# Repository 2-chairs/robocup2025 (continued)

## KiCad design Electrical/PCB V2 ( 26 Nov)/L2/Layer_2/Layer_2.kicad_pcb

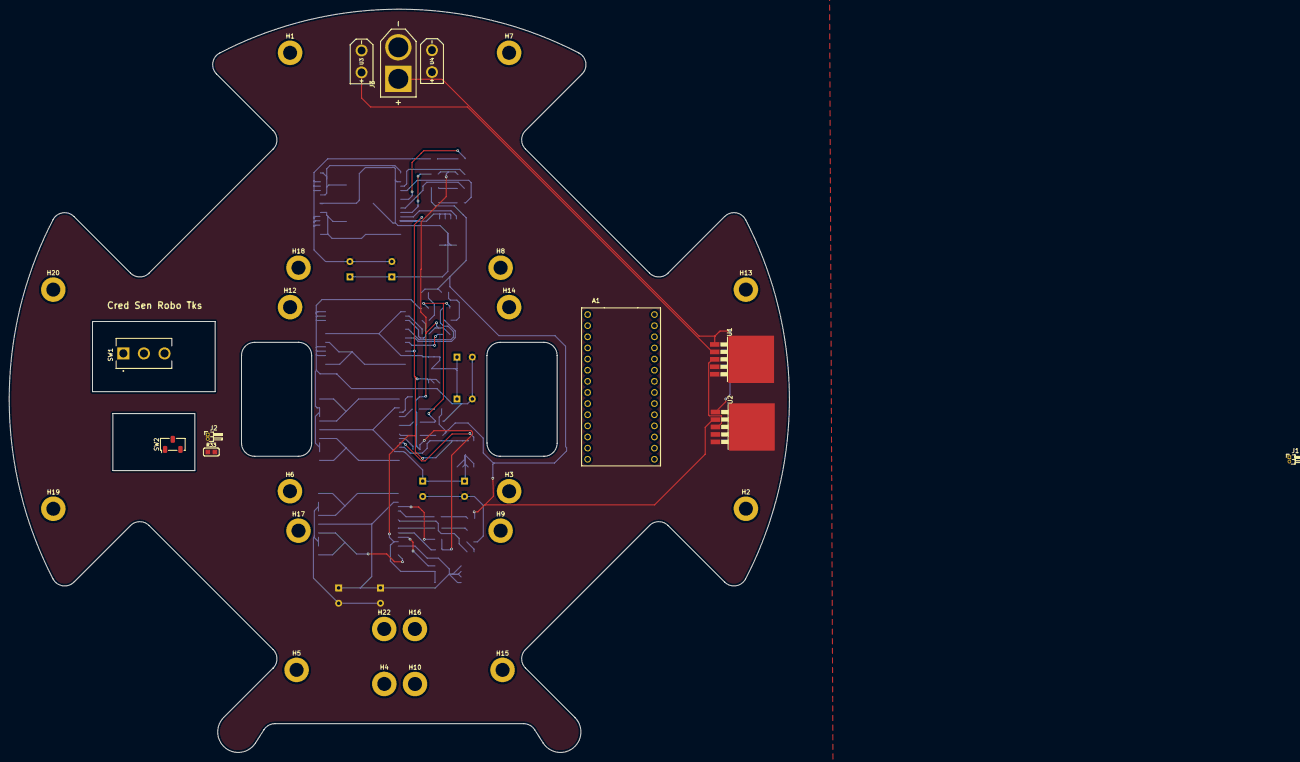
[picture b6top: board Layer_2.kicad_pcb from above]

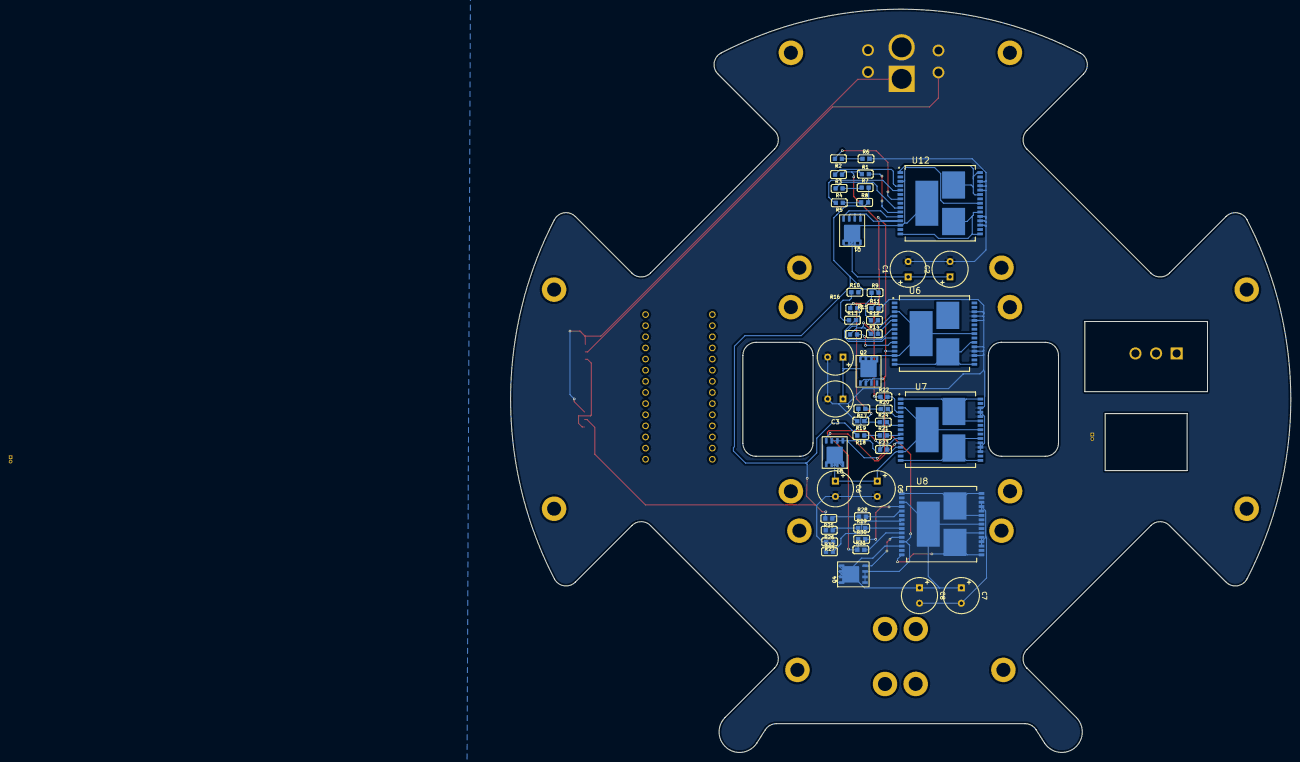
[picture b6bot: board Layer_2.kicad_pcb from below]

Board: 2 copper layers, 178.0 x 169.6 mm, 79 parts (48 on the bottom side), 55 nets.

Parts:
A1: TEENSY_4.0; Teensy 4.0
C1, C2, C3, C4, C5, C6, C7, C8: 470u; CP_Radial_D8.0mm_P3.50mm
H1, H2, H3, H4, H5, H6, H7, H8, H9, H10, H12, H13, H14, H15, H16, H17, H18, H19, H20, H22: MountingHole; MountingHole_3.2mm_M3_DIN965_Pad
J1, J2: Conn_01x02; PinHeader_1x02_P1.00mm_Horizontal
J3: XT60-M; AMASS_XT60-M
Q1, Q2, Q3, Q4: AON6354; 8-DFN (5x6)
R1, R2, R3, R4, R5, R12, R13, R14, R15, R16, R20, R21, R22, R23, R24, R28, R29, R30, R31, R32, R33: 1K; res0603
R6, R11, R19, R27: 10K; res0603
R7, R8, R9, R10, R17, R18, R25, R26: 3K3; res0603
SW1: SW_Push; SW_100SP1T1B4M2QE
SW2: SW_Nidec_CAS-120A1; Nidec_Copal_CAS-120A
U1, U2: LM2596ADJ
U3, U4: XT30UPB-M
U6, U7, U8, U12: VNH5019ATR-E; IC_VNH5019ATR-E

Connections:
+3V3: R7.2, R8.2, R9.2, R10.2, R17.2, R18.2, R25.2, R26.2, U2.2 (OUT), U4.P$1 (+)
+12V: Q1.1 (S), Q1.2 (S), Q1.3 (S), Q2.1 (S), Q2.2 (S), Q2.3 (S), Q3.1 (S), Q3.2 (S), Q3.3 (S), Q4.1 (S), Q4.2 (S), Q4.3 (S), R33.2, U6.12 (VBAT), U7.12 (VBAT), U8.12 (VBAT), U12.12 (VBAT)
/5v: U1.2 (OUT), U3.P$1 (+)
/12v: J3.P (POS), SW1.2, U1.1 (VIN), U2.1 (VIN)
/Motor 1 ENA: R5.1, R8.1
/Motor 1 ENB: R4.1, R7.1
/Motor 1 Out A: U12.1 (OUTA), U12.25 (OUTA), U12.30 (OUTA), U12.HS2 (OUTA)
/Motor 1 Out B: U12.15 (OUTB), U12.16 (OUTB), U12.21 (OUTB), U12.HS3 (OUTB)
/Motor 2 ENA: R9.1, R12.1
/Motor 2 ENB: R10.1, R13.1
/Motor 2 Out A: U6.1 (OUTA), U6.25 (OUTA), U6.30 (OUTA), U6.HS2 (OUTA)
/Motor 2 Out B: U6.15 (OUTB), U6.16 (OUTB), U6.21 (OUTB), U6.HS3 (OUTB)
/Motor 3 ENA: R17.1, R20.1
/Motor 3 ENB: R18.1, R21.1
/Motor 3 Out A: U7.1 (OUTA), U7.25 (OUTA), U7.30 (OUTA), U7.HS2 (OUTA)
/Motor 3 Out B: U7.15 (OUTB), U7.16 (OUTB), U7.21 (OUTB), U7.HS3 (OUTB)
/Motor 4 ENA: R25.1, R28.1
/Motor 4 ENB: R26.1, R29.1
/Motor 4 Out A: U8.1 (OUTA), U8.25 (OUTA), U8.30 (OUTA), U8.HS2 (OUTA)
/Motor 4 Out B: U8.15 (OUTB), U8.16 (OUTB), U8.21 (OUTB), U8.HS3 (OUTB)
/Motor Driver: J2.1, R1.1, R3.1, R14.1, R15.1, R22.1, R23.1, R30.1, R31.1
/PWM Motor 1: R2.1, R6.1
/PWM Motor 2: R11.1, R16.1, R19.1, R24.1
/PWM Motor 4: R27.1, R32.1
GND: C1.2, C2.2, C3.2, C4.2, C5.2, C6.2, C7.2, C8.2, J3.N (NEG), R6.2, R11.2, R19.2, R27.2, U1.3 (GND), U1.6 (GND), U2.3 (GND), U2.6 (GND), U3.P$2 (-), U4.P$2 (-), U6.18 (GNDB), U6.19 (GNDB), U6.20 (GNDB), U6.26 (GNDA), U6.27 (GNDA), U6.28 (GNDA), U7.18 (GNDB), U7.19 (GNDB), U7.20 (GNDB), U7.26 (GNDA), U7.27 (GNDA), U7.28 (GNDA), U8.18 (GNDB), U8.19 (GNDB), U8.20 (GNDB), U8.26 (GNDA), U8.27 (GNDA), U8.28 (GNDA), U12.18 (GNDB), U12.19 (GNDB), U12.20 (GNDB), U12.26 (GNDA), U12.27 (GNDA), U12.28 (GNDA)
unnamed: C1.1, C2.1, Q1.5 (D), Q1.6 (D), Q1.7 (D), Q1.8 (D), Q1.9 (D), U12.3 (VCC), U12.13 (VCC), U12.23 (VCC), U12.HS1 (VCC)
unnamed: C3.1, C4.1, Q2.5 (D), Q2.6 (D), Q2.7 (D), Q2.8 (D), Q2.9 (D), U6.3 (VCC), U6.13 (VCC), U6.23 (VCC), U6.HS1 (VCC)
unnamed: C5.1, C6.1, Q3.5 (D), Q3.6 (D), Q3.7 (D), Q3.8 (D), Q3.9 (D), U7.3 (VCC), U7.13 (VCC), U7.23 (VCC), U7.HS1 (VCC)
unnamed: C7.1, C8.1, Q4.5 (D), Q4.6 (D), Q4.7 (D), Q4.8 (D), Q4.9 (D), U8.3 (VCC), U8.13 (VCC), U8.23 (VCC), U8.HS1 (VCC)
unnamed: J2.2, SW2.2 (B)
unnamed: Q1.4 (G), U12.11 (CP)
unnamed: Q2.4 (G), U6.11 (CP)
unnamed: Q3.4 (G), U7.11 (CP)
unnamed: Q4.4 (G), U8.11 (CP)
unnamed: R33.1, SW2.3 (A)
unnamed: R12.2, U6.5 (ENA/DIAGA)
unnamed: R13.2, U6.9 (ENB/DIAGB)
unnamed: R14.2, U6.4 (INA)
unnamed: R15.2, U6.10 (INB)
unnamed: R16.2, U6.7 (PWM)
unnamed: R20.2, U7.5 (ENA/DIAGA)
unnamed: R21.2, U7.9 (ENB/DIAGB)
unnamed: R22.2, U7.4 (INA)
unnamed: R23.2, U7.10 (INB)
unnamed: R24.2, U7.7 (PWM)
unnamed: R28.2, U8.5 (ENA/DIAGA)
unnamed: R29.2, U8.9 (ENB/DIAGB)
unnamed: R30.2, U8.4 (INA)
unnamed: R31.2, U8.10 (INB)
unnamed: R32.2, U8.7 (PWM)
unnamed: R5.2, U12.5 (ENA/DIAGA)
unnamed: R4.2, U12.9 (ENB/DIAGB)
unnamed: R3.2, U12.4 (INA)
unnamed: R1.2, U12.10 (INB)
unnamed: R2.2, U12.7 (PWM)

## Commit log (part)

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2025-01-10 potato
2025-01-10 Update L2 Layout
2025-01-10 Create l2 layout v2
2025-01-10 4 motor drivers
2025-01-10 Created l2 edgecut dxf
2025-01-10 to be fix
2025-01-13 to do
    add sensor fix motor drivers and teensy
2025-01-13 2 more motor drivers to go!
2025-01-15 added l3 folder
2025-01-15 to be done : solve the teensy mystyery
2025-01-16 did ome stuff, added wheel both layers
2025-01-17 did some stuff
2025-01-18 added v1-v3 logos
2025-01-18 experimented with logo on silkscreen on l1, updated and cleaned up svg file to be ready for improting into kicad, decrases logo to 1cm2 size
2025-01-21 Update PCB V2 ( 26 Nov) before renaming
2025-01-21 renamed pcb v3
2025-01-22 did stuff
2025-01-22 rename
2025-01-22 added toshowup.txt to all folders to show up empty folders
2025-01-22 depresszion
2025-01-22 idk did some stuff
2025-01-22 updated l1 schematics
2025-01-22 renamed logo folder back to normal person naming scheme
2025-01-23 new bucky
2025-01-23 updated l2 dxfs
2025-01-23 did smth idk
2025-01-23 updated l2 dxf
2025-01-23 idk what this is either
2025-01-23 idk this too
2025-01-23 updated l2 layout, restarted on l1 pcb
2025-01-23 updated l2 layout again
2025-01-23 3 frivers add
2025-01-23 did mux wiring for l1
2025-01-24 24 JAN UPDATE
    LLOL
2025-01-24 TRY AGAIN 24 JAN
    NO DONT ASK
2025-01-24 I CHANGED THE NAME HEHEHEHEHE
    I LIKE DATES ON THE PROJECT :)))))))))
2025-01-24 2 motor controller
2025-01-24 did stuff (wrong)
2025-01-24 fix fills
2025-01-27 did smth
2025-01-27 tried
2025-01-31 Updated l2 dxf to v2
2025-02-01 updated l1 dxf to v2, l2 dxf to v3
2025-02-02 ignore this will be removed eventually
2025-02-02 mounting hole some issue idk
2025-02-05 added l2 dxf v4, started on l1 again
2025-02-05 added l3 v2, did some more l1
2025-02-05 updated l3
2025-02-05 Updated L3
    chen xuan wants to do when i gone
2025-02-05 halfway done with motor drivers footprint vias are gay
2025-02-05 finished l1?
2025-02-06 finished layer1?
2025-02-06 yay fixed motor driver do rest mr cos tired djbfj
2025-02-07 7 feb update!!! stop at pull up res
2025-02-07 cx is annoyingwith 1 drivers
2025-02-07 did somemore l1
2025-02-07 almost done with l1? more vetting done
2025-02-09 motor drivers someone done ish ig this is from yesterday
2025-02-09 last motor driver to be done and jst
2025-02-09 uploaded print files, added credits to l1
2025-02-09 Update README.md
    removed logo thats was not working
2025-02-09 Update README.md
    edited phrasing
2025-02-09 added logo v3 without brackets
2025-02-09 Update README.md
    added logo???
2025-02-09 Update README.md
    added logo and updated licesne
2025-02-09 Update README.md
    changed date
2025-02-09 Update README.md, added credits
    added credits
2025-02-09 motor drivers r done to be done tmr: diodes footbrint buckies boost capacitors and teensy pwm and motor feedback wiring
2025-02-10 what did i change dhvkdfgfk
2025-02-10 boostie
2025-02-10 edited l3 schematics
2025-02-10 i think i added the solenoid boost in this idk
2025-02-10 roughly finished l3
2025-02-10 added branding and credits to l3
2025-02-10 small adjustments made to l3 (moved a little silkscreen)
2025-02-10 kicad crashed ufekg still have like 70 errors
2025-02-10 something happened
2025-02-10 aestheticsjbbb to be done
2025-02-11 wt is this
2025-02-11 er constraints weirdo
2025-02-11 uncursed l3
2025-02-12 suffer
2025-02-12 lol why did i remove silkscreen
    in the title.😁
2025-02-12 spaced out l3 traces
2025-02-12 v4? v4 sounds cooler thasn v3
2025-02-12 v4 converted to v3 tho v4 sounds cooler than v3 and er one moter driver done buckies and boost done to be done is js teensy wiring anf drivers+l3jst
2025-02-13 allahhh almost done doing drc now
2025-02-13 fixed l1 and l3, awaiting vetting
2025-02-13 L1 & L3 APPROVED BY HAOYUN
2025-02-13 something happened to l1 or l3
2025-02-14 removed acute angles from l3
2025-02-14 fixed l1 and l3
2025-02-14 no idea what happened to l3 and l1 but they changed
2025-02-14 pls no conflict
2025-02-14 added some changes kianwu suggested to l1 (changed clearences etc)
2025-02-15 show new l1 to haoyuun shd be somewhat done @Ng-Chen-Xuan if need make some tweaks
2025-02-15 pcb shd be done errors are footprint problmes idk if we shd ignore
2025-02-15 did via stitching for l1
2025-02-15 idk why this stuff is here
2025-02-15 new version
2025-02-15 fixed abit of l2
2025-02-15 idk erm yea
2025-02-15 fixed?
2025-02-15 made l2 more to my liking
2025-02-15 why didnt this get committed too
2025-02-17 traumna
2025-02-17 done besides rx tx
2025-02-17 swap rx tx
2025-02-17 removed ONE acute angle from l3
2025-02-18 what did i doooo
2025-02-18 fix errors?!
2025-02-18 tried to fix some gay looking stuff
2025-02-19 new bom
2025-02-19 added all bom files
2025-02-19 added v5 l2 dxf
2025-02-19 redid l1 to fit new solenoid, updated l2 dxf to v6
2025-02-19 new gay dxf
2025-02-19 new footprint for tps
2025-02-19 redid l1 to fit new solenoid mounting
2025-02-20 deleted zips folder becuz it doesnt look good
2025-02-20 haoyun vetting
2025-02-20 cursed
2025-02-21 js feel like pushing
2025-02-21 kinda gay
2025-02-21 fixed l1 boost, started on activation circuit
2025-02-21 oops forogt to close apps first
2025-02-21 fixed l1 solenoid mosfet
2025-02-22 uncursed
2025-02-22 kinda ugly test poinY
2025-02-22 updated tp footprint, added library
2025-02-22 erm curses
2025-02-22 updated custom testpoint
2025-02-22 cursed trace silkscreen overlap
2025-02-22 somewhat did boost pcb. pending improvements
2025-02-22 cx try to uncurse some weird traces if any
2025-02-22 added zip cos haoyun
2025-02-22 somewhat finished l1, need to improve and un uglify
2025-02-22 exported l1 step file, added some 3d models to l1, spammed save
2025-02-22 closed kicad
2025-02-23 adjusted l1 abit, still peninging l1 redo
2025-02-23 2 new jsts
2025-02-23 new pos of esp and jst on l1
2025-02-23 redid l1
2025-02-23 lets goooo
2025-02-23 shhhh
2025-02-23 i think im done with everything haoyun gave all clear
2025-02-23 fixed diode and activation cirucit for solenoid (l1), exported step files of all layers
2025-02-24 i think ii need to change er tjst idk to where though
2025-02-24 did some stuff (added 3d model for sth)
2025-02-24 hgshjdjuk
2025-02-24 walao who changed the readme
2025-02-24 switched l3 jst
2025-02-24 removed led ring silkscreen for l1, switch 12v jst to xt30
2025-02-24 ergb
2025-02-24 added l2 dxf v7
2025-02-25 did alot of stuff
2025-02-26 added extrelmly dumb and waste og time l2 step
2025-02-26 centered diode
2025-02-26 make some fills nicer, exported new l1 3c model
2025-02-26 added new l2 xtmodel becuz im dumb
2025-02-26 updated l3 3d model
2025-02-26 flipped l3 jst, added l3 step
2025-02-26 added l3 new step, added new testpoint, fixed some l3
2025-02-26 fixed l3, added new l3 model
2025-02-26 added l2 dxf v8
2025-02-26 next jst
2025-02-26 me tired
2025-02-26 DHMN V D
2025-02-26 added some stuff to parts list, fixed l1 schematics to fit parts in lab abit more, pending change of activaition circuit
2025-02-26 deleted some l3 stuff to clear up folders, open and closed l3
2025-02-26 am i done im tired
2025-02-27 did some touching up made traces less cursed with gnd fills in between and made schmeatics look better with aligned boxes
2025-02-27 solved 3v3 thingy for l2
2025-02-27 added new tps
2025-02-27 ok testpoints
2025-02-27 added stitch vias
2025-02-27 uncursed 12v trace
2025-02-28 did nothing
2025-02-28 nothimngh done again
2025-02-28 finally done
    please dont blow up
2025-02-28 did drc
2025-02-28 fixed l1 solenoid activation circuit
2025-02-28 added l1 step
2025-02-28 mopved caps
2025-02-28 fixed caps again
2025-02-28 did something with l1
2025-02-28 did nothingi idk why i have commits but js incase ill push them
2025-02-28 fixed l2 caps positon, export new l2 step. fixed l3 jst from eh to xh, realised need to flip l2 jst
2025-02-28 fixed l2 switch jst position,
2025-02-28 added 3d model for nuke switch xt30
2025-02-28 exported new l2 step
2025-02-28 fixed l3 edge cut in 5min what an accomplishment
2025-02-28 exported new l3 step, closed kicad
2025-03-01 shopuld have fixed l1 and l3 based on kian wu comments
2025-03-01 uncursed some traces on l2
2025-03-01 new step
2025-03-01 closed kicad lol
2025-03-02 hope this works
2025-03-02 NEWER STEP
2025-03-02 newer step and less cursed traces
2025-03-02 i kinda forgot what else i changed i js got a new bom
2025-03-02 newer new step
2025-03-02 uncursed traces
2025-03-03 change l3 files to kicad 9, made ONE trace look nicer
2025-03-03 dshxkvfsdk half way done want to sleep
2025-03-03 made more chaneifugkbd
2025-03-03 idl symmerty seems very cursed idk
2025-03-03 ugly ill try to solve it js iignore this ig
2025-03-03 Revert "ugly ill try to solve it js iignore this ig"
    This reverts commit 7661a4ec2d23ca034bc6a6c45d6a88a4925001ca.
2025-03-03 its not corrupted!!!!
2025-03-03 erm moved 2 drivers flip
2025-03-03 hope tyhis works
2025-03-04 newer newer step
2025-03-05 make some traces less cursed for l2
2025-03-05 UNCURSED some MORE l2
2025-03-05 fixed l2
2025-03-05 added new l2 dxf
2025-03-05 added new l1 dxf
2025-03-05 added new l2 dxf again
2025-03-05 did alot of uncursing
2025-03-05 added new dxf for l1 and l2
2025-03-05 added new l1 and l2 dxf AGAIN
2025-03-05 hope this newer ver works cx edited abit
2025-03-05 exported l1 3d model
2025-03-05 exported new l2 3d model
2025-03-05 did sth, probably change l1 to kicad 9
2025-03-05 updare steppy
2025-03-06 fixed l1 jst position
2025-03-06 did some changes to l2 still need to link everything up pos are symmetric though
2025-03-06 ugly buck
2025-03-06 tidied up 3v3 buck
2025-03-06 change l1 1x4jst pos
2025-03-06 edited l1
2025-03-06 swapped l1 rx n tx
2025-03-06 have not started on drivers buckies seem done idk
2025-03-06 fixed l2. IM A GENIUS I CREATED RULE AREA
2025-03-06 did a bit of drivers maybe finish tmr idk
2025-03-07 added 3v3
2025-03-07 finished 1 motor drievr
2025-03-07 new l2 dxf
2025-03-07 finiahed buck
2025-03-07 wdois;iugEIl:oaU
2025-03-07 changed l1 credits
2025-03-07 allahhh
2025-03-07 new l2 dxf again again
2025-03-07 new l2 dxf agian agian again
2025-03-08 how thisa is final version
2025-03-08 fix teensy
2025-03-08 fixed l2, exported new l2 and l3 steps
2025-03-08 exported new l1 step
2025-03-08 fixed problems drc found on l2
2025-03-08 changed 3v3
2025-03-08 bot renders (v220)
2025-03-09 new shell 3mf
2025-03-09 fix except mosfet
2025-03-09 spamed vias lol
2025-03-09 i think i fixed everything
2025-03-09 erm increased the angle thing of 2 bcu on l3 jst
2025-03-09 fixed l2 and l3, new l2 and l3 step
2025-03-09 fixed l2 n l3, production files for all layers, step for l2 and l3
2025-03-10 deleted 2 random lines from l2 schematics
2025-03-10 new production files in case
2025-03-12 added butter chicken
2025-03-12 new read me thats funny
2025-03-14 added new roller mech files
2025-03-14 added new mech files
2025-03-14 adedd prusaslcier config files
2025-03-15 created print files for rollers
2025-03-18 added prodcution files for l1
2025-03-18 fixed l1
2025-03-18 fixed l1 pcb
2025-03-19 idk if i fixed l1 code
2025-03-19 fixed? removed A from analog pin definitions
2025-03-21 fixed l2 bucks
2025-03-24 wrote l2 code
2025-03-25 reorganised code, wrote l3 code
2025-03-26 did some code
2025-03-26 wrote code
2025-03-27 wrote more code
2025-03-29 fixed wheels and proabbly kicker
2025-04-01 did some stufdf
2025-04-01 did l1 code
2025-04-01 new mech files
2025-04-03 wrote coide (l1 uart)
2025-04-03 wrote more code!!!!
2025-04-03 MOTORS SPIN!!!
2025-04-03 new print files, theoretical movement code from chatgpt
2025-04-04 hhehheheheheharrrr
    chen xuan shouting at yikai to save code, what happens next is shocking
2025-04-04 used chat gpt try tofs
2025-04-04 house
    haoyuan hoouse vvv big hor (camera success)
2025-04-04 Update main.cpp (wrote code)
2025-04-04 did changes to cam code and l3
2025-04-04 wrote l2 cam communication code
2025-04-04 i coooked
    yo
2025-04-04 read cam values
2025-04-05 write l2 start code
2025-04-05 l2 code
2025-04-05 write moverobot code
2025-04-05 cam code?
2025-04-05 somewhatworking code
2025-04-05 yikai imu
2025-04-05 deltedted l2 code
2025-04-05 theoratically write l2 code
2025-04-06 uygdwok
